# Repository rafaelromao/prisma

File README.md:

# Prisma

A wireless Choc v1 split keyboard: the handwired Diamond's 1333+2 layout on one
reversible PCB per half, a XIAO-sized nRF52840 module, and a 7 × 20 × 40 mm (500 mAh)
battery in each half. The halves join magnetically into a unibody, or stack back to
back for transport. The [project page](https://rafaelromao.github.io/prisma/) has the
boards, renders, BOM and build guide on one page.

## One board, either module

The board takes a Seeed XIAO nRF52840 (the genuine one) or a NologoTech Super52840
(also sold as "MINI NRF52840", "NRF52840 RE:1.4"). Both have the same 14 edge pins
on the same nRF52840 pins, so the firmware is the same; they differ underneath,
where the board reaches the battery, the 12th key and reset:

- **Battery.** Their battery pads are in the same two spots, but swapped: the XIAO's
  + (VBAT) is the pad nearer the module's middle, the Super52840's + (B+) the one
  nearer the USB end. A **battery selector** on the switch face picks which hole is
  +: bridge the row labelled `+MID` for a XIAO, `+USB` for a Super52840. Never both:
  that shorts the battery.
- **12th key (P0.09).** The XIAO's NFC1 pad, or the Super52840's P0.09 pad in its row
  of nine extra GPIO pads: a hole under each, on the same net. Under a XIAO, the
  Super52840's hole touches its NFC2 pad (P0.10), which is unused and idle.
- **Reset** is in the same place on both.
- The Super52840's USB-C legs come through its board: the PCB has clearance holes
  under them, and its USB-C sticks out 0.8 mm further, which the case's recess takes.

The Super52840's pads were measured from several photos, beside a ruler, against the
2.54 mm pin pitch. Its USB-C sits 0.3 to 0.6 mm off centre, towards the D0–D6 pins, so
the leg clearance holes, the notch in the board edge and the case's recess all allow
for that either way (its RST, GND and SWD pads land within 0.2 mm of the XIAO's). The
battery holes are small and sit inside both modules' pads, at least 0.25 mm from the
Super52840's GPIO row under the other half's module, wherever between the two photos'
readings that row really is.

| | |
|---|---|
| Keys | 24 (12 per half): 3×3, one pinky key, two thumbs, all 1u Choc |
| Key layout | The Diamond's angles and stagger (from `body_right.stl`), packed at Choc spacing (18 × 17 mm) |
| PCB | 87.6 × 92.3 mm, 2 layers, 1.6 mm, reversible: one design, order 5. Same cut-diamond outline, so two boards side by side form the diamond. A notch in the edge in front of the USB-C lets a cable's overmold reach the port |
| Wiring | Diodeless, one pin per key (11 Xiao pins + NFC1) |
| Case | Solid base, a pocket per part (0.6 mm clearance), 0.5 mm around the PCB and plate (0.3 at the seam), 93 × 100.5 mm per half at the girdle (the rim is 91.6 × 96.5), with a 45° chamfer under it; tent 6.6°; 20.4 mm at the seam, 10.5 mm at the outer edge (plate included, keycaps excluded). Five pad slots under the floor (below) |
| Anti-slip pads | 5 × 8×2 mm silicone bump-ons per half, as on the original Diamond's base: each slot under the floor (8.6 mm wide, 1.1 deep) holds two pad spots, 8.7 mm apart. Each half sticks its pad in a different end, so stacked, each pad drops into the other half's empty end and the floors (and magnets) still meet. Every key centre sits at least 2.8 mm inside each half's pads, so a press on a border key can't tip it |
| Top plate | Covers the whole board: 1.2 mm Choc v1 plate, 1.0 mm over the PCB (the flange sits 2.2 mm up), 14.0 mm cutouts (`cut_tol` 0.1 per side), a 0.5 mm pocket over the Xiao area for solder blobs, a pocket and cone over the reset button, support pillars, countersunk screw bosses, chamfered bottom edge |
| Power | XIAO nRF52840 or Super52840, 500 mAh 1S LiPo (nominal 7 × 20 × 40 mm) on a JST PH 2.0 socket, MSK-12C02 power switch next to the USB port on the lower outer facet. The wall has a recess the size of a USB-C overmold (14.6 × 7.4 mm, rounded corners, room for a module whose port sits off centre) in front of the port, and a slot open to the top for the lever, widening outwards for a fingernail, with a rounded floor |
| Reset | A 5.1 × 5.1 × 2.0 mm SMD tact switch (TS-1187A) on the switch face, in the nook between the index finger's bottom key and the thumbs, 7.6 mm from the nearest keycap. It reaches through a 45° cone in the plate (4.2 mm across at the top, 2.8 at the throat) with its plunger 0.2 mm under the plate's top: a fingertip presses it, keycaps and palms don't. Press once to reboot, twice for the bootloader, with the case closed |
| Screws | 4 × M3 × 8 flat head (90° countersunk) per half: through the plate and PCB, self-tapping into the solid Nylon base (2.5 mm pilot). `SCREW` in `design.py` switches to heat-set inserts |
| Magnets | One part everywhere: 8 × 1.5 mm N52 discs. Each half has 13: 4 original stacking positions, 3 stand contacts on a circle around the estimated centre of gravity, and 6 evenly spread across the inner wall at 17.8 mm pitch. Every pocket keeps 0.5 mm of plastic all round |
| Assembly | Iron only: no reflow-only parts |

The 500 mAh bay moves the battery away from the inner seam and raises the PCB **1.8 mm**,
keeping the existing 6.6° tent, PCB outline, connector and screw-hole positions. The nominal
7 × 20 × 40 mm finished pack is checked with a 7.5 × 20.5 × 41 mm envelope and the case's
clearance. Measure the actual protected pack, including tabs and wire exit, before printing;
never compress a pouch cell to make it fit. The electrical board and pin map are unchanged.
The trackball and trackpad use smaller 752025, 250 mAh batteries.

Use the half cases, dock and module parts from the same version together: their front facets and
heights are matched.

## Independent tenting on the Ugreen's tilting platform

Each half has three extra floor magnets on a **44 mm circle**, spaced **120° apart** around
the estimated assembled centre of gravity. The pattern is derived from a mass-weighted model
of the nylon case, PCB, battery, switches and magnets, checked by `stand_mount.py`; it is not
a measured balance point. Use two **steel tilting phone platforms**, not the stands' bases.
The owner has tested the platforms and confirmed that they attract magnets. The existing
case magnets attach directly: **no extra platform magnets or glue are required**.
All ten possible foot positions lie outside the centred 54 mm circular contact patch,
with at least **11.55 mm planar edge clearance**. They do not create an air gap there.
Keep the case magnets flush and adhesive off their faces. A larger or noncircular platform
must be checked against the feet, rubber coverings, lips and other obstructions separately.
The estimated gravity projection remains inside the three-contact triangle through 35° of tilt;
this does not certify the magnets' holding force or the stand's own stability.

`python3 stand_mount.py` checks the group and writes 1:1 alignment templates (not glue guides):
[left](case/stand_magnet_template_left.svg), [right](case/stand_magnet_template_right.svg).
Print at 100%: the dashed contact boundary is **54 mm** across; the magnet-centre circle is 44 mm.
That is the required clear flat
patch, **not a confirmed Ugreen measurement**. The 54 mm circle leaves only 1 mm from an
8 mm magnet's edge to the platform edge; prefer about **60 mm** where the real platform
still clears all feet. Measure its shape and surface before use. Steel attraction is confirmed,
but slip/peel resistance, typing loads and stability at the chosen tilt still need a physical
load test. Aluminium and nonmagnetic stainless steel are unsuitable; some stainless grades
are magnetic, so test the actual platform. The render uses an illustrative stand/platform.

## Before ordering

The board is made in one batch, so check what software can't:

1. **Print** `fab/print_1to1_F_face.pdf` and `fab/print_1to1_B_face.pdf` at 100 % ("Actual
   size", no fit to page). The board outline must measure 87.55 mm across.
2. **Lay the real parts on the prints**, each on the face it's soldered to. The module's
   castellations go over the edge pads, with its USB-C at the board edge. A Choc switch's pins and
   pegs go over one key's holes, and its hot-swap socket over the socket pads on the other face.
   Then the JST socket, the MSK-12C02 (its two pegs in the small holes) and the reset button.
3. **Super52840:** on the print, its B+ and B- pads must cover the two holes in the battery box,
   its `009` pad the round hole in the P0.09 box, and its USB-C legs land inside the two pairs of
   slots. Measure its height from its underside to the top of its USB-C shell: the case allows
   4.3 mm (the XIAO's).
4. **Firmware:** rebuild it before flashing (`b prisma -c` in rafaelromao/keyboards, branch
   `prisma`). `check_pcb.py` confirms that branch lists the board's pins, given the shield's
   `prisma_peripheral_left.overlay` and `_right.overlay` copied to `.render/fw_left.overlay`
   and `.render/fw_right.overlay`.

Checked by the scripts: JLCPCB's limits in the DRC (`pcb/prisma.kicad_dru`: annular ring
 0.18, pad holes 0.45 apart, tracks and clearance 0.10, silkscreen 1.0 mm text with a 0.15 stroke),
no tracks under the module's antenna, every net against its intent and the firmware's pin lists
(`check_pcb.py`), both modules' underside pads against the board's copper, and every part, plug,
screw, magnet and pad against the case (`check_fit.py`).

**Fabrication gate:** the battery holes have a 0.6 mm drill in a 0.96 mm pad: a **0.18 mm
annular ring**, the configured absolute minimum, not the 0.25 mm recommendation. The small
ring preserves the underside-pad and routing clearances; do not enlarge it without rerouting
and rechecking both module options. Obtain the fabricator's explicit acceptance of these
holes before ordering. A clean DRC does not establish production yield.

## Files

| Path | What |
|---|---|
| `fab/prisma_jlcpcb.zip` | Gerbers + drill files: upload to JLCPCB as they are |
| `fab/print_1to1_F_face.pdf`, `fab/print_1to1_B_face.pdf` | Both faces at full size, to lay the real parts on before ordering |
| `pcb/` | The KiCad 9 project, its footprint library, 3D stand-ins, and DRC rules |
| `case/case_left.stl`, `case/case_right.stl` | The printed base |
| `case/plate_left.stl`, `case/plate_right.stl` | The printed top plate, oriented top face down for printing |
| `case/dock.stl`, `case/insert.stl` | The cyberdeck dock, and the placeholder for its drawer (below) |
| `stls/` | The same printable parts under print-friendly names: case and plate left/right, dock, drawer insert, module tray, and the trackball/trackpad lids |
| `stand_mount.py`, `case/stand_magnet_template_*.svg` | Independent-stand contact check and 1:1 platform-magnet templates |
| `trackball/`, `trackpad/` | The drawer modules: scripts, `case/` STLs; the trackball's board in `pcb/` and `fab/` |
| `zmk/` | The modules' ZMK shields |
| `renders/` | Board, board with parts, case, full build; `all.png` has every view on one sheet |
| `BOM.md` | Parts list (AliExpress search terms) |
| `BUILD.md` | Hand-soldering and assembly guide, testing, printing |
| `index.html` | The project on one page: both boards, the renders, the BOM and the build guide (also served as the GitHub Pages home) |
| `design.png` | Top view of the placement: sockets (red), Xiao, battery, JST, magnets, screws, the reset button (red, its cone white), pad slots (grey: left pads filled, the right half's dashed) |
| `renders/pads.png` | Both floors from below: where each half's pads go |
| `*.py`, `*.sh` | The generators: everything above is built from them |

## Renders

| Board, top | Board, bottom |
|---|---|
|  |  |
| **Left half with parts, top** | **Left half with parts, bottom** |
|  |  |
| **Case** | **Full build, side (the tent)** |
|  |  |
| **Top plate** | **Top plate, underside** |
|  |  |
| **Joined as a unibody** | **Joined, from above** |
|  |  |
| **Stacked back to back** | **Stacked, side** |
|  |  |

## Cyberdeck dock

A phone on a Ugreen folding stand (base 85 × 105 × 4 mm) is the computer and the screen;
`dock.py` makes one printed part, `case/dock.stl`, that holds both halves around it. Without the
stand it is a tented, splayed unibody, sturdier than the magnets at the seam alone.

- **Over the stand's base**, in a pocket in its underside: the base keeps its own feet on the
  desk and carries the phone. Behind the spine the base is left bare, its hinge (`HINGE`,
  30 × 28 mm, estimated from photos: measure yours) 0.5 mm (`HINGE_CLR`) off the halves, the
  wings and the spine, as far forward as their back corners let it. The pocket's fit holds the
  dock on the base, together with three pairs of the common **8 × 1.5 mm magnets**: three pressed
  into the pocket's roof and three glued on the aluminium base. The tent also keeps room for
  both discs and their backing below the drawer floor.
- **The board's lower half:** under each half's girdle, its widest line, every wall of the dock
  carries on the case's own 45° bottom chamfer down to the desk, one flat plane with it, front,
  back and sides, wings and spine alike. Each wall is built as a plane through its girdle edge, so
  none can fold. Below the girdle the spine and the wings are one piece; above it the spine stops
  0.2 mm short of the seam walls. The wing ends just short of the outer pad, which stands on the
  desk, and each pad recess is shaped to its bump-on's dome so none breaks out of a wall.
- **The halves on wings** the shape of their floors, inner side up, outer pad on the desk, splayed
  12° (`SPLAY`). The extra tent is the least that keeps 1.6 mm of plastic over the base and room
  under the magnets: 5.70°, about 12.3° in all. Every pad slot has a recess, both ends.
- **A spine** between the halves, level with their seam walls' top edges, its front and back
  carrying on both halves' walls, its point cut to a flat as wide as the joined board's front
  flat (about 20 mm). Its middle is a **drawer** (`DRAWER`), pulled out through the front, for a module
  (below) or the **placeholder** (`insert.py`, `case/insert.stl`): a solid block with the modules'
  outline and magnets, flush with the halves, the joined board's diamond cut into its top, and
  **PRISMA** in 0.5 mm low relief behind it. The
  drawer is open at both the top and the front. Its sides are straight and uninterrupted: no
  raised ends at the mouth, no ribs or matching grooves. The insert's front is shaped in 3D by
  the halves' exact front facet planes, rather than set back to a vertical wall, so the assembled
  front reads as one element. To take one out, push the tip of its rear hood forwards through the
  rear passage, then pull it out of the front. Lifting is not necessary.
- **Six side magnets per half:** the dock's continuous walls are 2.4 mm thick at their
  thinnest and house six of the common **8 × 1.5 mm N52 magnets per side**, matching all six
  half seam magnets. The gap between the halves is widened by 1.25 mm to preserve insert space.
  Load them from outside, flush, and glue them in; a verified **0.6 mm inner skin** retains them
  inside. Each faces the keyboard half directly outside and the insert's own matching magnet
  through the inner wall at three of those positions. The insert still has only three side
  magnets per side, evenly spaced at y = -7.0, 28.6 and 64.2 mm (seam magnets 2, 4 and
  6, every other magnet in the six-position row). The same insert magnets meet either half directly on the desk.
  Check magnetic holding force with real magnets before relying on it to carry the assembly.
- **A magnet under each pointing module:** one more 8 × 1.5 mm N52 disc in the module's floor and its
  mate in the drawer floor, on the centreline at y = −48.3 mm. Only three underside stand contacts are used, so at least 1 mm of plastic remains between opposing pocket envelopes, even with each pocket 0.2 mm off.
  The rear stays free for USB-C and the power switch.
- **Lap use:** the rear hood recess and USB passage remove material from the dock spine, and an
  insert is not bonded to it. Test a printed dock under load before relying on it for lap use.
- **Magnets in the wings** under six of each half's seven floor magnets. `MAG_COST` rejects
  positions that would add more than 1° to the tent needed for the base pocket. `MAG_ROOF`
  keeps 1 mm under a pocket over the base. Pockets near a 45° wall are nudged inwards to retain
  their surrounding plastic without losing alignment with the case's magnet.
- **Feet:** the underside is cut 0.5 mm (`FOOT_LIFT`) off the desk, and three 8 × 2 mm bump-ons
  under each wing, spread to the largest triangle, make that up.
- 199.0 × 111.3 × 29.8 mm, about 83 cm³. `python3 dock.py` prints the fit check: each half, its pads, the
  base and the hinge against the dock, all 0 mm³, and the plastic round every magnet and foot.

| **With the phone** | **From the front** |
|---|---|
|  |  |
| **Without the stand: a unibody** | **From the side** |
|  |  |
| **The dock** | **Underneath** |
|  |  |

## Drawer modules: a trackball or a trackpad

Two standalone ZMK pointing devices. Either slides into the dock's drawer from the front, or snaps onto
either half's inner wall on the desk, or sits on its own on its bump-ons. They are built like a half: a
tray, a lid, and the same M3 × 8 flat-head screws from the top. The tray is one print, shared by every
module; only the lid changes.

- **Shared by both:** the tray, the main board (keys, hot-swap sockets, power switch), a controller on its own small board,
  a 752025 (250 mAh) battery, and a sensor board holding the reset button. All in the same places, so the
  power slider, the USB-C port and the reset hole are in the same spot on every module.
- **Retention:** three common magnets a side where the halves' inner-wall magnets are (the 2nd, 4th and
  6th), at the same height over the plane both stand on, plus one in the floor over its mate in the drawer.

| **Trackball** | **The parts** |
|---|---|
|  |  |
| **Choc v1 lid, same tray and boards** | **Inside (cut through the middle)** |
|  |  |
| **On a half, on the desk** | **Its boards (front / back)** |
|  |   |
| **Trackpad** | **The parts** |
|  |  |
| **On a half, on the desk** | **The placeholder in the drawer** |
|  |  |

### USB-C

The USB-C port is flush with the module's back, under the power slider, with no wall or floor beneath it,
so a plug goes straight in. The dock has a **12.8 mm wide rear passage all the way down through the
underside**: the nominal model allows a 12.35 × 6.5 mm overmold; check the actual plug and print. At the rear the module's top
extends over the dock's sloped support: the common underside and its mating support are 45°, with 0.4 mm
clearance.

| Trackball: rear connection | Cutaway to the receptacle |
|---|---|
|  |  |
| Trackpad: rear connection | Cutaway to the receptacle |
|  |  |
| Trackball docked | Trackpad docked |
|  |  |

### Prisma Trackball (`trackball/trackball.py`)

A 34 mm ball and two MX or Choc v1 hot-swap keys on one shared PCB. The MX lid stands 4 mm over the
halves; the Choc lid 1.2 mm. Their front and side upper facets run from the halves' top height to the lid top. The front facet is steeper to preserve the 40 mm trackpad rim and key/power-switch clearance; the lower front remains matched to the drawer.

- The ball sits in a cup in the lid on three 3 mm Si3N4 balls and lifts straight out. Under it, a PMW3610
  on its own board looks up through an LM18-LSI lens (circuit after siderakb's pmw3610-pcb, CERN-OHL-P-2.0,
  at 3.3 V logic with a TLV74318).
- The main board accepts **MX or Choc v1 hot-swap sockets**, not both populated together. Choc sockets
  face 180° opposite the MX sockets. MX uses `trackball/case/lid.stl` (1.5 mm plate), Choc uses
  `trackball/case/lid_choc.stl` (1.2 mm plate). Choc v2 is not supported.
- The controller stands face down on a standard 2.54 mm header on its own small board, its USB-C port
  flush with the back wall. That board drops into the tray between printed stops, which take a plug's force.
- Eight 15 mm stacking pins join the controller board to the main board, beside the controller, and the battery and reset
  come by wire from the controller's own pads to `VBAT` and `R2`. The main board does not lift out once they are soldered.
  The sensor's SCLK, SDIO (3-wire SPI), NCS and MOTION go to pads `CK`, `IO`, `CS` and `MO`. Each pad takes one
  controller pin, on both modules; the table is in `BUILD.md`, and in `trackball/controller_pinout.py`.
- One panel to order (`trackball/fab/trackball_jlcpcb.zip`), 53.7 × 99.5 mm: the main board and the
  sensor board at opposite ends of a long bridge, with a row of snap holes at each end, and the
  controller board on a short tab off the sensor board's side.
  `trackball/route.sh` builds, routes and checks it (`build_pcb.py`, Freerouting, DRC).
- **One orderable panel for nice!nano v2 or plain XIAO nRF52840:** both stand on the same header. Rows 5 to 7 are
  GPIOs on both, so the signals differ only in firmware. One solder jumper chooses the 3.3 V pin:
  a nice!nano has VCC in row 4 where a XIAO has 3V3 in row 3. Its pin rows sit 0.2 mm further back than a
  nice!nano's, so a XIAO's USB-C mouth lies 0.2 mm inside the rear plane. The tray's seats and stops clear the
  Seeed STEP reference, but actual revisions, clones, wiring and retention still need checking.
- The sensor's posts print 0.4 mm low. Equal shims can adjust the optical gap, but the real ball-to-board
  distance and lens reference-plane height must be measured; see `BUILD.md` for the calculation and limits.
  Finish the two sensor-board screws to **≤7.6 mm overall** and deburr them outside the assembly.
  Head seating in the straight PCB hole consumes 0.22 mm in the model; verify at least 0.3 mm
  tip clearance and adequate engagement at the actual shim thickness before installing the battery.
  The four lid screws remain M3 × 8, unmodified.

### Prisma Trackpad (`trackpad/trackpad.py`)

The same module with a 40 mm Cirque (TM040040, I²C) in the lid instead of the ball. It uses the Choc
sockets on the shared main board and stands at the Choc lid's height, 1.2 mm over the halves.

- Use compact **17.5 × 16.5 mm Choc caps**. Conventional twin-stem caps rotate with the
  switch, putting **17.5 mm front-to-back** here; they cannot be independently quarter-turned.
  The centred nominal pad-to-cap gap is **0.585 mm**; an 18 mm square envelope has only
  **0.335 mm**. The seat's 0.3 mm radial allowance can reduce these to **0.285/0.035 mm**
  before print error or wobble. Check actual pad placement, adhesive, cap travel and wobble;
  these are not first-print fit guarantees. The front screw centres are now
  x = ±21.0, y = −91.5 mm, leaving **2.087 mm** from the countersink envelope to the pad seat
  (formerly 0.871 mm). Use the new tray and lids together; PCB holes and key positions are unchanged.

- Retain the supplied I²C breakout with its pull-up resistors and original 12-pin flat cable.
  Four wires connect the MCU to the breakout; one separate DR wire connects the MCU directly to the
  Cirque underside. The sensor/reset board area reserves a 24 × 18 × 4.5 mm breakout envelope on a
  2.5 mm insulating spacer, plus cable-bend room, with no printed holder. Verify actual kit dimensions.

| Wire | nice!nano v2 | Plain XIAO nRF52840 |
|---|---|---|
| Breakout SDA, on pad `IO` | D3 (P0.20) | D5 (P0.05) |
| Breakout SCL, on pad `CK` | D2 (P0.17) | D4 (P0.04) |
| Cirque DR, separate underside wire, on pad `MO` | D4 (P0.22) | D6 (P1.11) |
| Breakout GND, VDD | GND, VCC (3.3 V) | GND, 3V3 |
| Main board K1, K2 | D19 (P0.02), D21 (P0.31) | D7 (P1.12), D9 (P1.14) |
| Main board `G`, by stacking pin | GND | GND |
| Main board `VBAT`, `R2`, by wire | B+, RST | BAT+, reset pad |

Use I²C at address `0x2A`; confirm R1 is absent on an SPI-labelled kit and leave R7/R8 fitted for
3.3 V operation.

**Firmware** (`zmk/`): a ZMK config with both shields, `prisma_trackball` (the PMW3610 through
badjeff's zmk-pmw3610-driver) and `prisma_trackpad` (the Cirque through Zephyr's in-tree
Pinnacle driver), pinned in `zmk/config/west.yml`. Key 1 clicks left; key 2 clicks right, and
held turns pointing into scrolling; both together click middle. If the pointer runs the wrong way,
check the selected driver's orientation settings against its binding before changing the overlay.

`python3 -m unittest test_stl_export test_half_battery test_drawer test_module_assembly test_xiao_option trackball.test_layout`
runs the checks.

For the XIAO shields, initialize a west workspace from `zmk/config/west.yml`, then build ZMK's `app`
for `xiao_ble//zmk` with `SHIELD=prisma_trackball_xiao` or `prisma_trackpad_xiao` and
`ZMK_EXTRA_MODULES` set to this directory's absolute `zmk/` path. For example, from that workspace:

```sh
west build -s zmk/app -d build-trackball -b xiao_ble//zmk -- -DSHIELD=prisma_trackball_xiao -DZMK_EXTRA_MODULES=/absolute/path/to/prisma/zmk
west build -s zmk/app -d build-trackpad -b xiao_ble//zmk -- -DSHIELD=prisma_trackpad_xiao -DZMK_EXTRA_MODULES=/absolute/path/to/prisma/zmk
```

The generated `zephyr/zmk.uf2` is controller-specific. Compilation is not a physical sensor, charging or Bluetooth test.

## How a reversible board makes two halves

The left half gets its parts on the bottom (B) face. The right half is the same
board turned over, so its parts go on the F face. Silkscreen says which face is
which (`LEFT: parts on this face`).

Turned over, the Xiao's pins land mirrored: where the left half has D0, D1 and D2,
the right half has VBUS, GND and 3V3. Those three pins reach their keys through
solder jumpers. **Bridge the three jumpers on the face without the Xiao** (inside its
outline, labelled D0–D2) and leave the other three open. The other eight edge pins
are GPIO either way. The firmware just lists different pins per half.

Diodeless needs 12 inputs and the Xiao's edge only has 11, so the 12th key uses
the NFC1 pad on the Xiao's underside, through a plated hole you solder from the
other face. NFC itself is not used.

The reset button is wired the same way: the Xiao's reset test pad (pad 17 in
Seeed's footprint, `EN` in their symbol; TP2 on the nRF52840's P0.18/RESET in
Seeed's schematic) is reached through a plated hole filled from the switch face,
and the button joins it to GND. Each half's reset hole has its own net (`RST_L`,
`RST_R`) wired only to that half's button pads: turned over, one half's reset
hole lands under the other half's GND test pad. No pin changes, so the firmware
is unaffected.

Pin map (from `pcb/pinout.json`):

| Key | Left | Right |
|---|---|---|
| pinky | D0 | D0 |
| ring top / home / bottom | D4 / D3 / D1 | D9 / D10 / D1 |
| middle top / home / bottom | D5 / D2 / D6 | D8 / D2 / D7 |
| index top / home / bottom | NFC1 / D7 / D8 | NFC1 / D6 / D5 |
| thumb outer / inner | D9 / D10 | D4 / D3 |

## Firmware

ZMK shield `prisma` in [rafaelromao/keyboards](https://github.com/rafaelromao/keyboards)
(`zmk/keyboards/rafaelromao/prisma`). It builds for `xiao_ble//zmk` with the
same keymap as the other Diamonds:

```sh
b prisma -c   # central left, peripheral left/right, dongle
```

## Regenerating

Switch mounting dimensions and manufacturer sources are recorded in
[SWITCH_MOUNT_RESEARCH.md](SWITCH_MOUNT_RESEARCH.md). Choc module openings now match
the halves' 14.0 mm CAD aperture rather than reusing the MX lid's 14.2 mm aperture.
Printed snap retention still requires qualification with the selected switches/material.

See [PRINT_READINESS.md](PRINT_READINESS.md) for the pre-print acceptance gates. Nominal
collision tests do not qualify Nylon shrinkage, support removal, magnetic retention or a one-shot print.
The linked review's claim-by-claim results and independent blind-review follow-up are in
[PREPRINT_VERIFICATION.md](PREPRINT_VERIFICATION.md).

For a mechanical blind review or print-readiness review, apply [REVIEW_CHECKLIST.md](REVIEW_CHECKLIST.md), including opposing pockets in the populated assembly.

Requires Python 3 with `requirements.txt`, podman (KiCad 9 runs in the
`docker.io/kicad/kicad:9.0` image through `kicad.sh`), and Freerouting 2.x with
Java 25.

```sh
python3 design.py        # placement, tent, outlines, magnets, screws -> design.json, design.png
FREEROUTING=/path/freerouting.jar ./route.sh   # footprints, board, routing, pours, DRC
./fab.sh                 # gerbers and drill files -> fab/prisma_jlcpcb.zip
python3 magnets.py       # only after a layout change: measures the base for the magnets to pin in design.py
python3 case.py          # base and plate STLs (and their 3D models for renders)
python3 check_fit.py     # parts, plate, solder blobs, the reset button and its cone, screws, magnets, pad slots, a USB-C plug and the lever against
                         # the case, the pads stacked, and the pads' balance: all 0 mm³, ALL CLEAR
./kicad.sh python3 check_pcb.py   # every net against its intent, and the firmware's pin lists: ALL CLEAR
python3 dock.py          # the cyberdeck dock's STL, and its fit check: all 0 mm³
python3 trackball/trackball.py && ./trackball/route.sh && ./trackball/fab.sh   # the three-board panel and gerbers
./kicad.sh python3 trackball/check_controller_pcb.py   # every pad, header pin and jumper net
python3 trackpad/trackpad.py                       # trackpad module: case and fit check
python3 insert.py                                  # the drawer's placeholder
python3 vrml.py && python3 scene.py && ./kicad.sh python3 render_boards.py && ./render.sh
python3 page.py          # index.html's BOM and build-guide sections, from BOM.md and BUILD.md
```

`layout.py` holds the Diamond geometry. `design.py` places everything else and
holds the tolerances. The outline is the fewest-facet (`GEM_FACETS`) convex
polygon around both halves joined. `XIAO_SPOT` pins the Xiao's position;
set it to `None` to search again, and if the board won't route completely, try
the runners-up the search writes to `xiao_alternatives.json`. `RESET_SPOT` pins the reset button and `BUTTON` holds its datasheet heights
and the plate's pocket and cone; `design.py` asserts its clearances. `PAD_SLOTS` pins the
pad slots the same way (`None` searches again for the slots that keep every key
centre deepest inside both halves' pads). `MAG_FLOOR_SPOTS` and `MAG_SIDE_SPOTS` pin the
magnets, found by `magnets.py` against the solid base around the pads, parts and screws.

Credits: the Choc hot-swap footprint follows [kiswitch](https://github.com/kiswitch/kiswitch)
(MIT). The Xiao pad positions follow Seeed's
[OPL KiCad library](https://github.com/Seeed-Studio/OPL_Kicad_Library). The reset button's pads follow
KiCad's `Button_Switch_SMD:SW_SPST_TL3342` from the
[official footprint library](https://gitlab.com/kicad/libraries/kicad-footprints) (CC-BY-SA 4.0), which
matches XKB's TS-1187A land pattern.

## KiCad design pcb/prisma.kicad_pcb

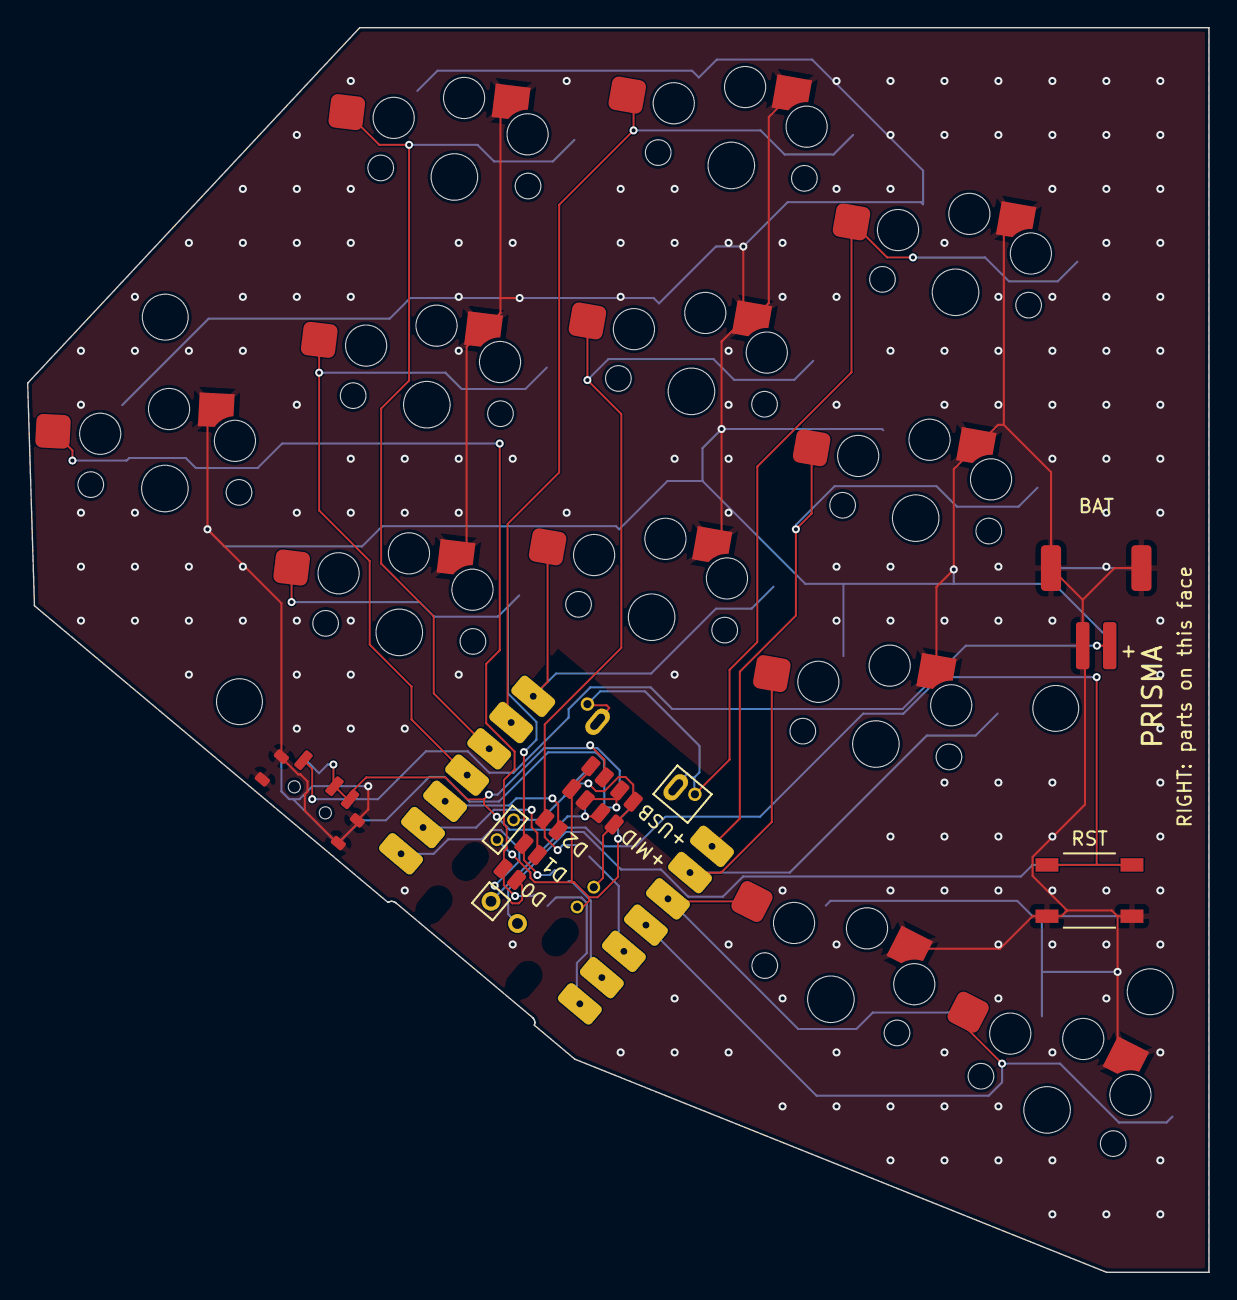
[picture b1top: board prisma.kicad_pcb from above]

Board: 2 copper layers, 87.6 x 92.3 mm, 34 parts (0 on the bottom side), 25 nets.

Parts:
H1, H2, H3, H4: M3; MountingHole_M3
J1: JST PH 2.0 battery; JST_PH_S2B_Reversible
JP1: D0 left; SolderJumper_F
JP2: D1 left; SolderJumper_F
JP3: D2 left; SolderJumper_F
JP12: D2 right; SolderJumper_B
JP13: D1 right; SolderJumper_B
JP14: D0 right; SolderJumper_B
JS1: +MID BATM; SolderJumper_F
JS2: +MID BATU; SolderJumper_F
JS3: +MID BATM; SolderJumper_B
JS4: +MID BATU; SolderJumper_B
JS5: +USB BATM; SolderJumper_F
JS6: +USB BATU; SolderJumper_F
JS7: +USB BATM; SolderJumper_B
JS8: +USB BATU; SolderJumper_B
SW1: pinky; SW_Choc_V1_Hotswap_Reversible
SW2: ring_top; SW_Choc_V1_Hotswap_Reversible
SW3: ring_home; SW_Choc_V1_Hotswap_Reversible
SW4: ring_bottom; SW_Choc_V1_Hotswap_Reversible
SW5: middle_top; SW_Choc_V1_Hotswap_Reversible
SW6: middle_home; SW_Choc_V1_Hotswap_Reversible
SW7: middle_bottom; SW_Choc_V1_Hotswap_Reversible
SW8: index_top; SW_Choc_V1_Hotswap_Reversible
SW9: index_home; SW_Choc_V1_Hotswap_Reversible
SW10: index_bottom; SW_Choc_V1_Hotswap_Reversible
SW11: thumb_outer; SW_Choc_V1_Hotswap_Reversible
SW12: thumb_inner; SW_Choc_V1_Hotswap_Reversible
SW13: MSK-12C02; SW_MSK12C02_Reversible
SW14: TS-1187A reset; SW_TS1187A_Reversible
U1: XIAO nRF52840 / Super52840; nRF52840_Module_Reversible

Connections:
BAT+: J1.1, SW13.1
BATM: JS1.1, JS3.2, JS5.1, JS7.2, U1.BATM
BATU: JS2.2, JS4.1, JS6.2, JS8.1, U1.BATU
GND: J1.2, J1.MP, JS2.1, JS4.2, JS5.2, JS7.1, SW1.1, SW2.1, SW3.1, SW4.1, SW5.1, SW6.1, SW7.1, SW8.1, SW9.1, SW10.1, SW11.1, SW12.1, SW13.SH, SW14.2, SW14.4
K_index_bottom: SW10.2, U1.L9
K_index_home: SW9.2, U1.L8
K_index_top: SW8.2, U1.NFC1
K_middle_bottom: SW7.2, U1.L7
K_middle_home: JP3.2, JP12.2, SW6.2
K_middle_top: SW5.2, U1.L6
K_pinky: JP1.2, JP14.2, SW1.2
K_ring_bottom: JP2.2, JP13.2, SW4.2
K_ring_home: SW3.2, U1.L4
K_ring_top: SW2.2, U1.L5
K_thumb_inner: SW12.2, U1.L11
K_thumb_outer: SW11.2, U1.L10
RST_L: SW14.1, U1.RSTL
RST_R: SW14.3, U1.RSTR
VBAT: JS1.2, JS3.1, JS6.1, JS8.2, SW13.2, SW13.3
X_L1: JP1.1, U1.L1
X_L2: JP2.1, U1.L2
X_L3: JP3.1, U1.L3
X_L12: JP12.1, U1.L12
X_L13: JP13.1, U1.L13
X_L14: JP14.1, U1.L14
